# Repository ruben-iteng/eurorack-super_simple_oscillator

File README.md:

<div align="center">

# eurorack-super_simple_oscillator

<br/>

Eurorack modular synthesiser - Super Simple Oscillator

</div>

## About

<div align="center">

</div>

A super simple oscillator module (avalanche vco) in eurorack format based the designs of [Look Mum No Computer](https://www.lookmumnocomputer.com/projects#/simplest-oscillator) and [kassutronics](https://kassu2000.blogspot.com/2018/07/avalance-vco.html).
This project is build with the opensource EDA [faebryk](https://github.com/faebryk/faebryk).

## What can you do with this project?

You can use this project in various ways.
You can use it:

- as template for a faebryk project
- to build this VCO for your eurorack synth
- to design your own thing based on this design

## Working with the source files

See [here](./docs/development.md) for the instructions on how to install and edit this project.

## Building the SSO module

If you want to build a physical SSO eurorack module you can find the build instructions [here](./docs/build_instructions.md).

## Contibuting

If you want to share your alterations, improvements, or add bugfixes to this project, please take a look at the [contributing guidelines](./docs/CONTRIBUTING.md).

## Community Support

Community support is provided via Discord; see the Resources below for details.

### Resources

- Source Code: [https://github.com/ruben-iteng/eurorack-super_simple_oscillator](https://github.com/ruben-iteng/eurorack-super_simple_oscillator)
- Chat: Real-time chat happens in faebryk's Discord Server (chit-chat room for now). Use this Discord [Invite](https://discord.gg/95jYuPmnUW) to register
- Issues: [https://github.com/ruben-iteng/eurorack-super_simple_oscillator/issues](https://github.com/ruben-iteng/eurorack-super_simple_oscillator/issues)

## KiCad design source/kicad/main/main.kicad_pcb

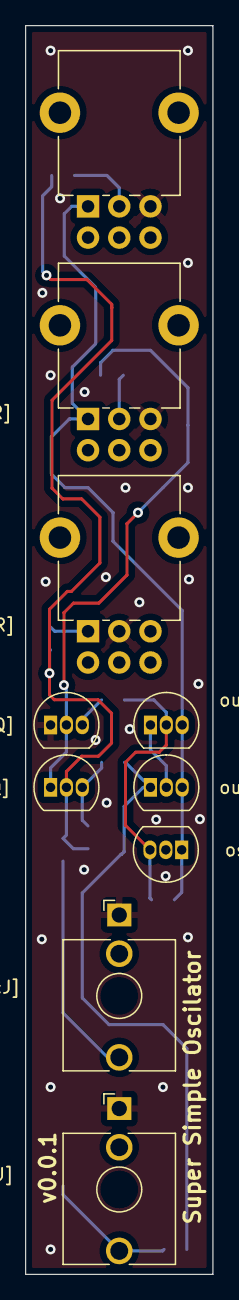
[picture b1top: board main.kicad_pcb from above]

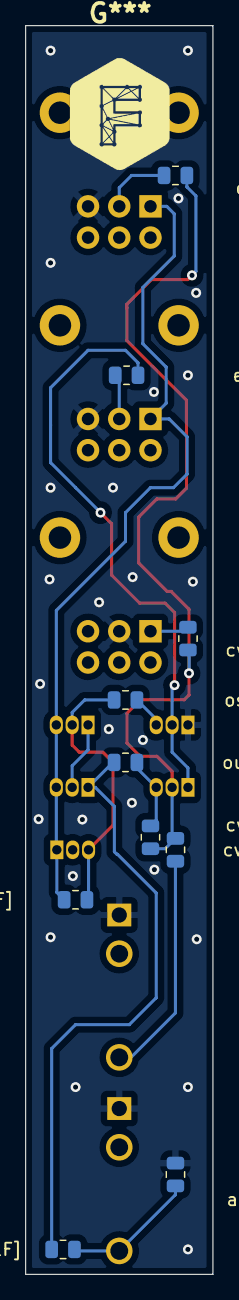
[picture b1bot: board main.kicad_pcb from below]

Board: 2 copper layers, 15.0 x 100.0 mm, 20 parts (10 on the bottom side), 14 nets.

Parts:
audio_output.ac_coupling_capacitor[Capacitor:9.999999999999998µF]: 9.999999999999998µF; R_0805_2012Metric
audio_output.jack[AudioJack2_Ground:J]: J; Jack_3.5mm_QingPu_WQP-PJ398SM_Vertical_CircularHoles
audio_output.pull_down_resistor[Resistor:10KΩ]: 10KΩ; R_0805_2012Metric
cv_input.freq_devider_mix_resistor[Resistor:150KΩ]: 150KΩ; R_0805_2012Metric
cv_input.frequency_control_potentiometer[Potentiometer:R], cv_input.voct_scale_trimmer[Potentiometer:R]: R; Potentiometer_Alpha_RD902F-40-00D_Dual_Vertical_CircularHol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
cv_input.input_impendace_resistor[Resistor:100KΩ]: 100KΩ; R_0805_2012Metric
cv_input.input_jack[AudioJack2_Ground:J]: J; Jack_3.5mm_QingPu_WQP-PJ398SM_Vertical_CircularHoles
cv_input.negative_bias_resistor[Resistor:220KΩ]: 220KΩ; R_0805_2012Metric
cv_input.voct_min_resistor[Resistor:1.0KΩ]: 1.0KΩ; R_0805_2012Metric
expo_converter.buffer[_2N3906:Q], expo_converter.current_sink[_2N3904:Q]: Q; TO-92_Inline
expo_converter.frequency_offset_current_min_resistor[Resistor:100KΩ]: 100KΩ; R_0805_2012Metric
expo_converter.frequency_offset_trimmer[Potentiometer:R]: R; Potentiometer_Alpha_RD902F-40-00D_Dual_Vertical_CircularHol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
osc_core.charge_capacitor[Capacitor:10.0µF]: 10.0µF; R_0805_2012Metric
osc_core.current_limiting_resistor[Resistor:1KΩ]: 1KΩ; R_0805_2012Metric
osc_core.reverse_avalanche_transistor[_2N3904:Q]: Q; TO-92_Inline
output_buffer.current_limiting_resistor[Resistor:10KΩ]: 10KΩ; R_0805_2012Metric
output_buffer.stages[0][_2N3904:Q], output_buffer.stages[1][_2N3904:Q]: Q; TO-92_Inline

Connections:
[Kassutronics_Avalance_VCO:virt]-cv_input[cv_input:virt]:2-cv_input.voct_scale_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: audio_output.jack[AudioJack2_Ground:J].S, audio_output.pull_down_resistor[Resisto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.2, cv_input.frequency_control_potentiomete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.3, cv_input.input_jack[AudioJack2_Ground:J].S, cv_input.voct_scale_trimmer[Potentiomet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.2, expo_converter.current_sink[_2N3904:Q].1, expo_converter.frequency_offset_trimmer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.3
[Kassutronics_Avalance_VCO:virt]:3-cv_input[cv_input:virt]:4-expo_converter[exp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: cv_input.negative_bias_resistor[Resisto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.2, expo_converter.buffer[_2N3906:Q].3, output_buffer.current_limiting_resistor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.2
audio_output.ac_coupling_capacitor[Capacitor:9.999999999999998µF]-audio_output.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: audio_output.ac_coupling_capacitor[Capa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.2, audio_output.jack[AudioJack2_Ground:J].T, audio_output.pull_down_resistor[Resisto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.1
audio_output[audio_output:virt]:2-output_buffer[output_buffer:virt]:3: audio_output.ac_coupling_capacitor[Capa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.1, output_buffer.current_limiting_resistor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.1, output_buffer.stages[1][_2N3904:Q].1
cv_input.frequency_control_potentiometer.resistors[0][Resistor:virt]-output_buf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: cv_input.frequency_control_potentiomete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.1, expo_converter.frequency_offset_trimmer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.1, osc_core.charge_capacitor[Capacitor:10.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.2, osc_core.reverse_avalanche_transistor[_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.1, output_buffer.stages[0][_2N3904:Q].3, output_buffer.stages[1][_2N3904:Q].3
cv_input.frequency_control_potentiometer.resistors[0][Resistor:virt]:2-cv_input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: cv_input.freq_devider_mix_resistor[Resi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.2, cv_input.frequency_control_potentiomete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.2
cv_input.input_jack[AudioJack2_Ground:J]-cv_input.input_impendace_resistor[Resi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: cv_input.input_impendace_resistor[Resis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.1, cv_input.input_jack[AudioJack2_Ground:J].T
cv_input.voct_scale_trimmer.resistors[0][Resistor:virt]: cv_input.voct_min_resistor[Resistor:1.0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.2, cv_input.voct_scale_trimmer[Potentiomet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.1
cv_input[cv_input:virt]-expo_converter[expo_converter:virt]: cv_input.freq_devider_mix_resistor[Resi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.1, cv_input.input_impendace_resistor[Resis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.2, cv_input.negative_bias_resistor[Resisto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.1, cv_input.voct_min_resistor[Resistor:1.0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.1, expo_converter.buffer[_2N3906:Q].2
expo_converter.frequency_offset_current_min_resistor[Resistor:100KΩ]-expo_conve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: expo_converter.buffer[_2N3906:Q].1, expo_converter.current_sink[_2N3904:Q].2, expo_converter.frequency_offset_current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.1
expo_converter.frequency_offset_trimmer.resistors[0][Resistor:virt]:2-expo_conv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: expo_converter.frequency_offset_current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.2, expo_converter.frequency_offset_trimmer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.2
osc_core[osc_core:virt]-expo_converter[expo_converter:virt]:2: expo_converter.current_sink[_2N3904:Q].3, osc_core.current_limiting_resistor[Resi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.1
osc_core[osc_core:virt]:3-output_buffer[output_buffer:virt]:4: osc_core.charge_capacitor[Capacitor:10.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.1, osc_core.current_limiting_resistor[Resi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.2, osc_core.reverse_avalanche_transistor[_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.3, output_buffer.stages[0][_2N3904:Q].2
output_buffer.stages[1][_2N3904:Q]-output_buffer.stages[0][_2N3904:Q]: output_buffer.stages[0][_2N3904:Q].1, output_buffer.stages[1][_2N3904:Q].2

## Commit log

2022-07-01 Update to faebryk master
2022-07-01 Change to new trait system
2022-07-01 Format using Black
2022-07-01 Clean up
2022-07-15 udpates
2022-10-14 Bring up to working state
    - Add KiCad source files
    - Add KiCad files to gitignore
    - Fix component import
    - Fix typo in readme
    - Fix: make it run
    - Fix markdown rendering issue
2022-10-21 Add PCB image
2022-10-21 Prepare for new faebryk release
    - fix wrong connections
    - fix wrong resistor values
    - add missing pot
    - remove add_all function from local lib
2022-10-21 Fix image overlay text
2022-10-28 Fix: remove unnecessary pip requirements
2022-10-28 Fix netlist import from faebryk
2022-10-28 Merge pull request #1 from feature/update_for_faebryk_release
    * Add PCB image
    * Prepare for new faebryk release
    - fix wrong connections
    - fix wrong resistor values
    - add missing pot
    - remove add_all function from local lib
2022-10-28 Fix typos
2022-10-28 Add missing faebryk logo
2022-10-28 Adapt to CMPs and IFs to newest faebryk api
    Reload kicad converted libs
2022-11-04 Adapt CMPs and IFs to newest faebryk api (#3)
    Reload kicad converted libs
2022-11-04 Fix missing logo in library; Fix typos (#2)
    * Fix typos
    * Add missing faebryk logo

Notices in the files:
README.md:
License: MIT
